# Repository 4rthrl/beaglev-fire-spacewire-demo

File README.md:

# BeagleV-Fire SpaceWire Demo

This repository contains a complete SpaceWire demonstration running on two BeagleV-Fire boards.

The main BeagleV-Fire runs a ROS 2 Jazzy SpaceWire gateway. A second BeagleV-Fire emulates a camera and sends generated 64 × 64 RGB images over a physical SpaceWire link.

A PySide6 GUI on the PC communicates with the gateway over ROS 2/DDS and allows the user to:

- connect and disconnect the SpaceWire link;
- select an FPGA-generated image pattern;
- request and display an image;
- request camera housekeeping and inspect the decoded register snapshot;
- monitor SpaceWire diagnostics.

## Architecture

```text
PC
├── PySide6 GUI
├── ROS 2 Jazzy
└── diagnostic_aggregator
        │
        │ DDS / Ethernet
        ▼
Main BeagleV-Fire
├── ROS 2 SpaceWire gateway
├── SpaceWire FPGA core
└── DMA image receiver
        │
        │ SpaceWire
        ▼
Mock-camera BeagleV-Fire
└── FPGA camera emulator
```

## Repository structure

```text
board/
├── ros2_ws/        ROS 2 SpaceWire gateway
├── gateware/       Main-board and mock-camera FPGA bitstreams
├── debug/          Standalone SpaceWire debug tools
└── scripts/        Board setup, startup and programming scripts

pc/
├── gui/            PySide6 SpaceWire control GUI
├── ros2_ws/        PC-side ROS launch and diagnostics
├── setup_pc.sh
└── start_pc.sh

hardware/
└── connector_board/
    KiCad source, fabrication files and custom components

docs/
└── Detailed project documentation
```

## First-time setup

### PC

ROS 2 Jazzy is required.

```bash
./pc/setup_pc.sh
```

See [docs/installation.md](docs/installation.md) for the complete installation procedure.

### Main BeagleV-Fire

Copy the `board/` directory to the BeagleV-Fire and run:

```sh
./scripts/setup_board.sh
```

The main FPGA can be programmed with:

```sh
./scripts/program_main_board.sh
```

The mock-camera FPGA can be programmed on the second board with:

```sh
./scripts/program_mock_camera.sh
```

## Normal startup

On the main BeagleV-Fire:

```sh
./scripts/run_gateway.sh
```

On the PC:

```bash
./pc/start_pc.sh
```

The GUI can then be used to connect the SpaceWire link, request camera images and refresh camera housekeeping.

## Documentation

Detailed documentation is available in [`docs/`](docs/):

- [Installation](docs/installation.md)
- [Architecture](docs/architecture.md)
- [ROS 2 interface](docs/ros_interface.md)
- [Camera housekeeping registers](docs/camera_housekeeping_registers.md)
- [Hardware](docs/hardware.md)
- [Troubleshooting](docs/troubleshooting.md)

## License

Software in this repository is licensed under the Apache License 2.0 unless stated otherwise.

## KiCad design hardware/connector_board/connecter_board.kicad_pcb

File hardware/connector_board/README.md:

# SpaceWire Interface Board

This PCB is a compact SpaceWire interface board designed for use with the **BeagleV-Fire** platform through its SYZYGY connector.

The board converts FPGA logic-level Data and Strobe signals to/from LVDS for connection to a standard **9-pin Micro-D SpaceWire connector**. It is designed for SpaceWire data rates up to **400 Mbit/s**.

## Main features

- BeagleV-Fire / SYZYGY interface
- SpaceWire Data + Strobe transmit and receive
- Designed for up to **400 Mbit/s**
- 100 Ω differential SpaceWire routing
- Dual LVDS transmitter: **DS90LV027A**
- Dual LVDS receiver: **DS90LVRA2-Q1**
- 1.8 V / 3.3 V level translation for the FPGA interface
- 9-pin Micro-D SpaceWire connector
- 4-layer PCB with controlled-impedance differential routing

## SYZYGY compatibility

The board uses the standard SYZYGY physical connector and BeagleV-Fire pin interface, but it is **not intended to be a fully compliant generic SYZYGY peripheral**.

In particular, the board does not include the SYZYGY programming / identification circuitry or headers required for automatic SmartVIO configuration. It is intended specifically as a dedicated SpaceWire interface for the BeagleV-Fire setup.

## Purpose

The board was developed as part of a SpaceWire integration project to provide a clean physical interface between the BeagleV-Fire FPGA fabric and external SpaceWire equipment.

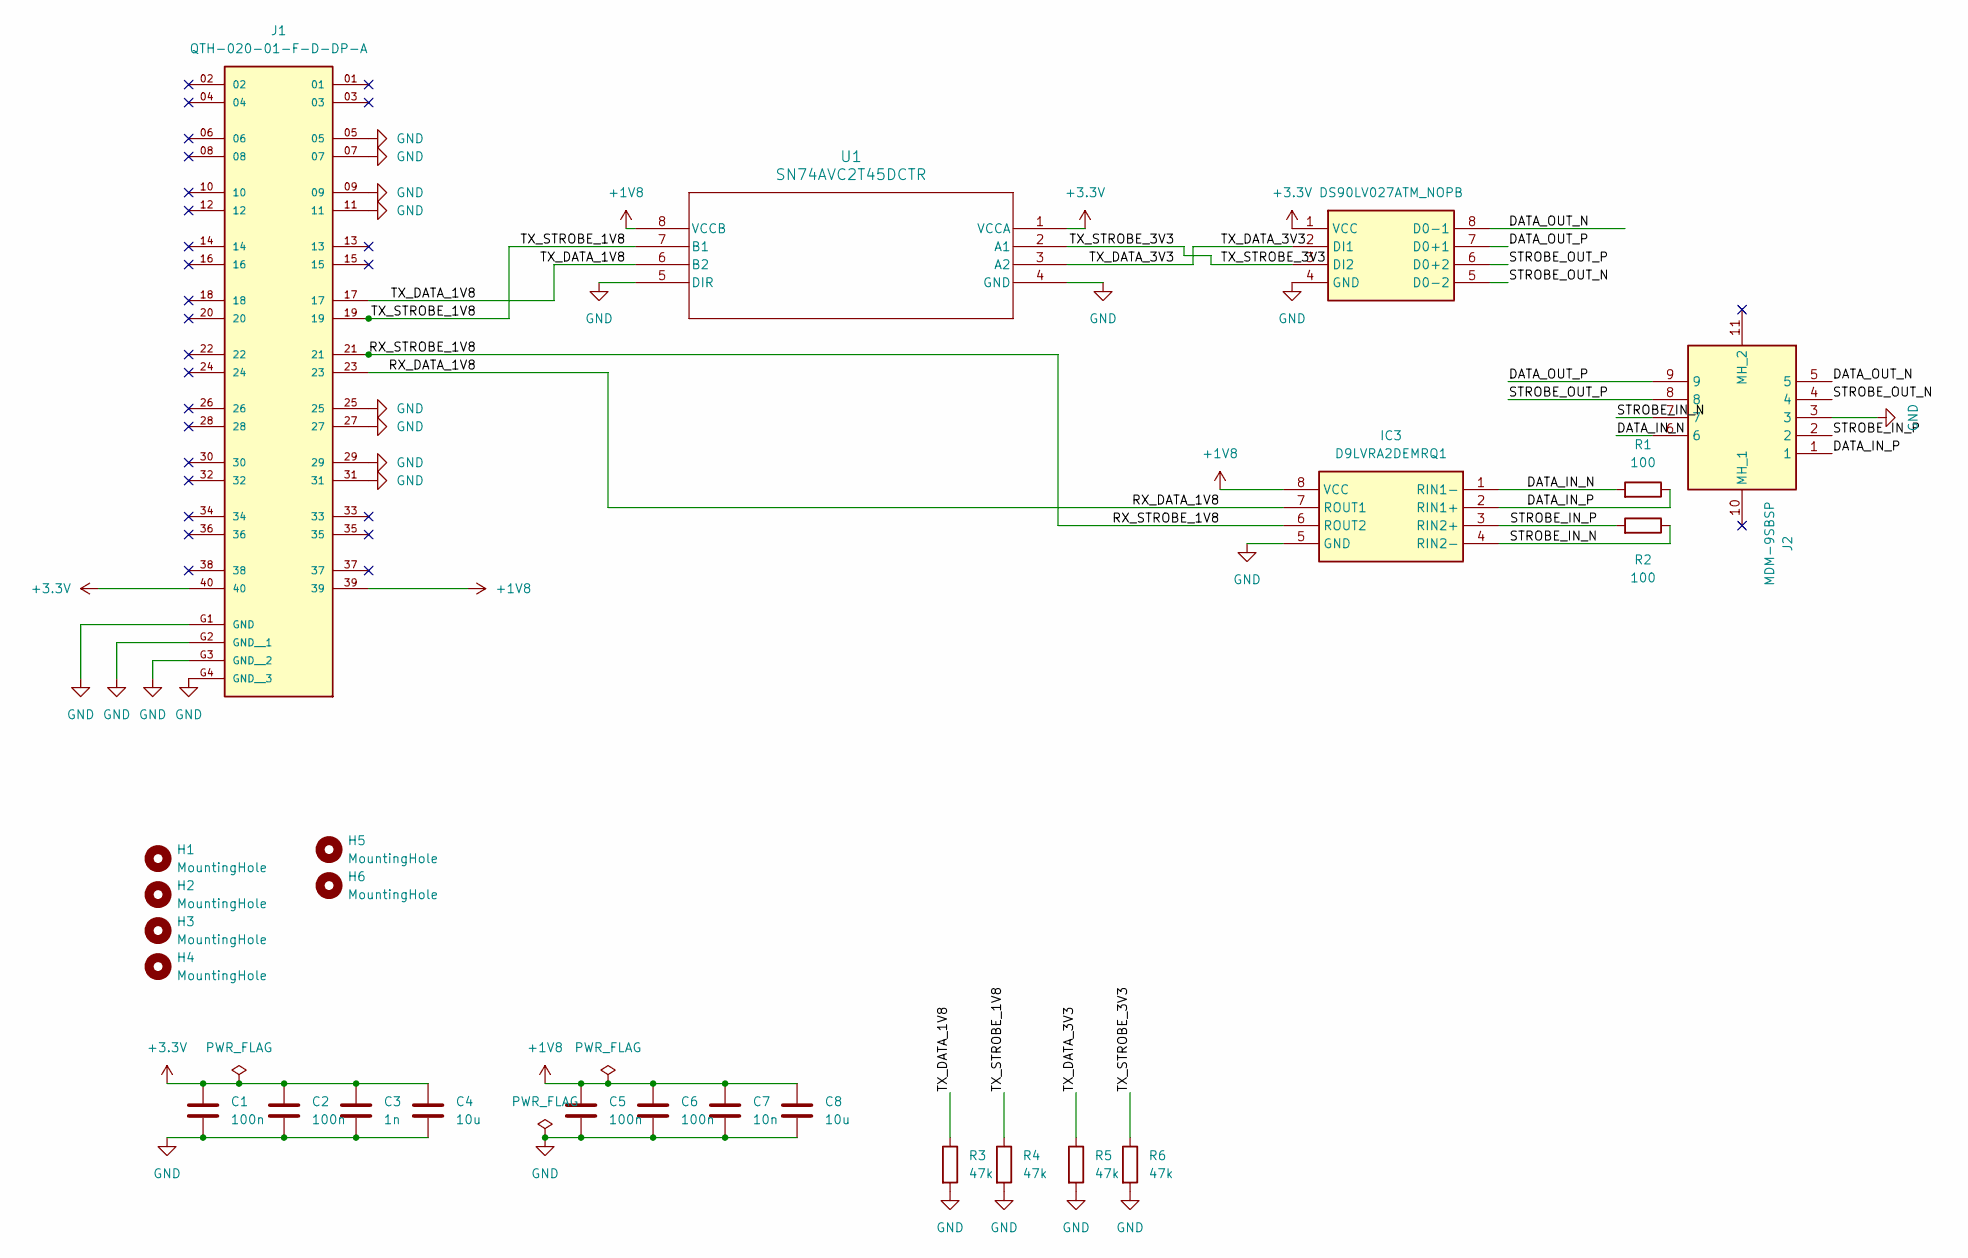
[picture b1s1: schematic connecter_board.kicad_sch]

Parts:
C1, C2, C5, C6: 100n; C_0603_1608Metric
C3: 1n; C_0603_1608Metric
C4, C8: 10u; C_0805_2012Metric
C7: 10n; C_0603_1608Metric
H1, H2: MountingHole; MountingHole_2.5mm
H3, H4, H5, H6: MountingHole; MountingHole_3.2mm_M3
IC2: DS90LV027ATM_NOPB; SOIC127P600X175-8N; Mouser Part Number 926-DS90LV027ATMNOPB
IC3: D9LVRA2DEMRQ1; SON50P200X200X80-8N; Mouser Part Number 595-D9LVRA2DEMRQ1
J1: QTH-020-01-F-D-DP-A; SAMTEC_QTH-020-01-X-D-DP-A; PARTREV L
J2: MDM-9SBSP; MDM9SBSP; Mouser Part Number 965-MDM-9SBSP
R1, R2: 100; R_0402_1005Metric
R3, R4, R5, R6: 47k; R_0603_1608Metric
U1: SN74AVC2T45DCTR; DCT8

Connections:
+1V8: C5.1, C6.1, C7.1, C8.1, IC3.8 (VCC), J1.39, U1.8 (VCCB)
+3.3V: C1.1, C2.1, C3.1, C4.1, IC2.1 (VCC), J1.40, U1.1 (VCCA)
/DATA_IN_N: IC3.1 (RIN1-), J2.6, R1.2
/DATA_IN_P: IC3.2 (RIN1+), J2.1, R1.1
/DATA_OUT_N: IC2.8 (D0-1), J2.5
/DATA_OUT_P: IC2.7 (D0+1), J2.9
/RX_DATA_1V8: IC3.7 (ROUT1), J1.23
/RX_STROBE_1V8: IC3.6 (ROUT2), J1.21
/STROBE_IN_N: IC3.4 (RIN2-), J2.7, R2.1
/STROBE_IN_P: IC3.3 (RIN2+), J2.2, R2.2
/STROBE_OUT_N: IC2.5 (D0-2), J2.4
/STROBE_OUT_P: IC2.6 (D0+2), J2.8
/TX_DATA_1V8: J1.17, R3.1, U1.6 (B2)
/TX_DATA_3V3: IC2.2 (DI1), R5.1, U1.3 (A2)
/TX_STROBE_1V8: J1.19, R4.1, U1.7 (B1)
/TX_STROBE_3V3: IC2.3 (DI2), R6.1, U1.2 (A1)
GND: C1.2, C2.2, C3.2, C4.2, C5.2, C6.2, C7.2, C8.2, IC2.4 (GND), IC3.5 (GND), J1.05, J1.07, J1.09, J1.11, J1.25, J1.27, J1.29, J1.31, J1.G1 (GND), J1.G2 (GND__1), J1.G3 (GND__2), J1.G4 (GND__3), J2.3, R3.2, R4.2, R5.2, R6.2, U1.4 (GND), U1.5 (DIR)

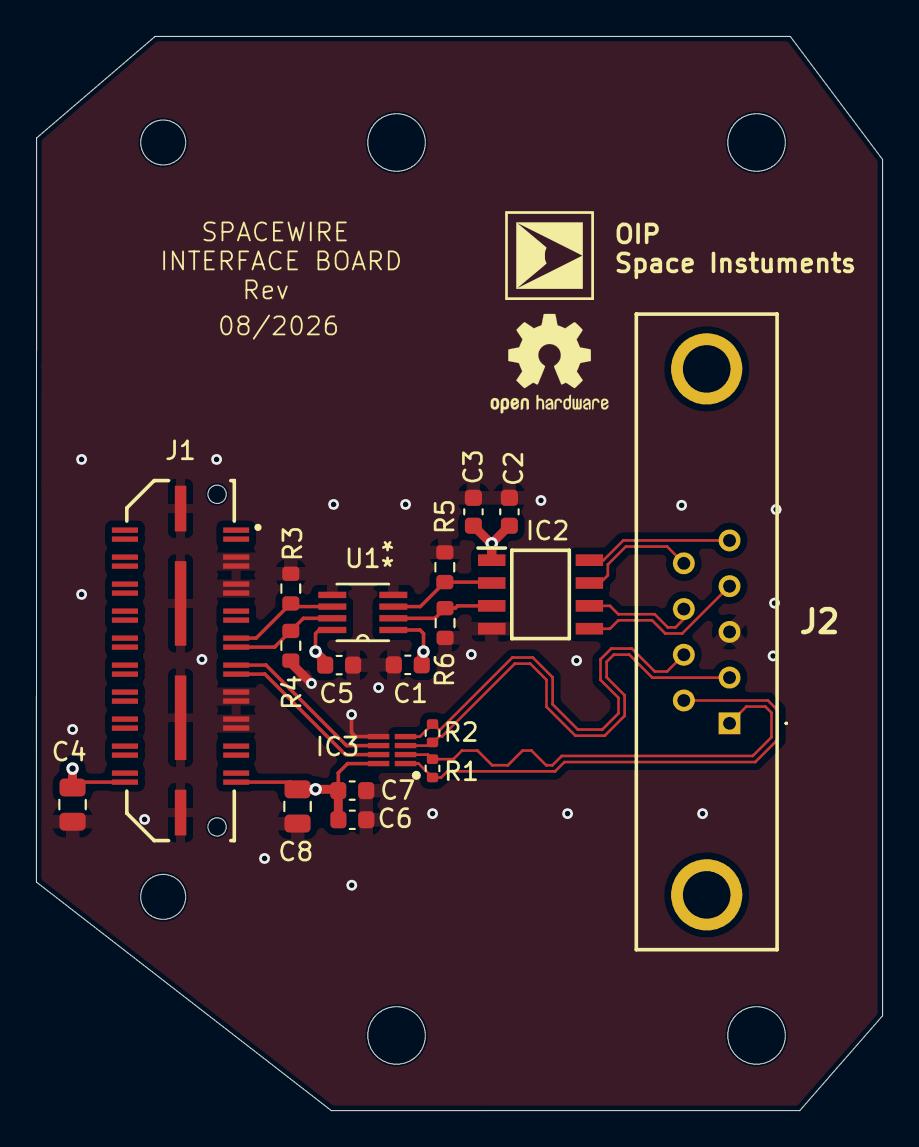
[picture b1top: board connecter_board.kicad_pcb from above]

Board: 4 copper layers, 47.0 x 59.7 mm, 25 parts (0 on the bottom side), 17 nets.
